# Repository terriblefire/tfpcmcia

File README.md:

# tfpcmcia

TerribleFire PCMCIA — a custom PCMCIA expansion card for the Amiga 1200 and Amiga 600, providing 4 MB fast RAM, an SD card interface, and 7 programmable RGB LEDs.

---

## Hardware

| Component | Part | Interface |
|-----------|------|-----------|
| Microcontroller | WCH CH32V307 (RISC-V, 144 MHz) | — |
| SPI RAM | APS6404L-3SQR, 4 MB | SPI1 @ 72 MHz |
| SD card | Standard microSD | SPI3 @ 36 MHz |
| LEDs | 7× APA102C RGB | GPIO (bit-banged) |

The card plugs into the Amiga's PCMCIA slot. The CH32V307 bridges the PCMCIA bus to an SPI RAM chip and SD card. The Amiga CPU accesses them entirely through memory-mapped reads and writes — the MCU handles all bus timing under interrupt.

---

## Memory Map

From the Amiga's perspective:

| Amiga address | Content | Notes |
|---------------|---------|-------|
| `$600000–$61FFFF` | Boot ROM (128 KB) | At power-on only; switches to SPIRAM after boot |
| `$620000–$9FFFFF` | SPIRAM (≈4 MB) | Fast RAM, available after driver init |
| `$A00000–$A001FF` | Attribute memory | PCMCIA CIS tuples (REG=1 accesses) |
| `$A20200–$A2023B` | I/O registers | Control, SPI, LED framebuffer |

The first 128 KB of SPIRAM overlaps the boot ROM window. After driver initialisation, `BOARD_CTRL` bit 0 is set, which switches that window from ROM to SPIRAM and makes the full 4 MB available as expansion memory.

---

## I/O Registers

All registers sit in PCMCIA I/O space. The Amiga's Gayle chip maps card I/O to `$A20000`; register byte offsets are relative to the card's I/O base (`0x220000`). The 68000 bus is 16 bits wide; each register occupies the upper byte of a 16-bit word (big-endian convention).

| Address | Offset | R/W | Name | Description |
|---------|--------|-----|------|-------------|
| `$A20200` | `0x200` | R/W | `SPI_DATA` | Write a byte to clock it out to the SD card; read to get the last byte clocked in |
| `$A20202` | `0x202` | W | `SPI_CS` | SD card chip select — `$00` = assert (active LOW), `$FF` = deassert |
| `$A20204` | `0x204` | R | `SPI_STATUS` | Bit 0: SD card detect (`1` = card present) |
| `$A20206` | `0x206` | R/W | `BOARD_CTRL` | Bit 0: `0` = boot ROM mapped, `1` = SPIRAM mapped; also controls LED mode |
| `$A20208` | `0x208` | R | `BOARD_ID` | Board identifier, always reads `$01` |
| `$A20220–$A2023B` | `0x220–0x23B` | W | `LED_FB` | LED framebuffer — 7 pixels × 4 bytes; see LED section |

---

## Boot Sequence

1. **CIS parsing** — Kickstart's `card.resource` reads the Card Information Structure from attribute memory (`$A00000`) and locates the `CISTPL_AMIGAXIP` (Execute-In-Place) tuple with the `AUTORUN` flag.

2. **XIP entry** — Kickstart calls `InitResident()` on the RomTag at `$600000`.

3. **Boot ROM init** — The ROM code:
   - Parses the embedded `tfpcmcia.device` (standard Amiga HUNK executable) from the ROM image
   - Allocates chip RAM, copies hunks, applies `HUNK_RELOC32` relocations
   - Calls `CacheClearU()` to flush CPU caches
   - Scans the loaded code for a RomTag and calls `InitResident()` on it

4. **Device init** — `tfpcmcia.device`:
   - Registers itself with Exec
   - Initialises the SD card via SPI (supports SDv1, SDv2, SDHC)
   - Creates an I/O task for asynchronous SD operations
   - Probes SPIRAM and, if present, adds a 1 MB block to the system free memory list (`AddMemList`, `MEMF_PUBLIC | MEMF_FAST`)
   - Scans the SD card for an RDB (Rigid Disk Block)

5. **RDB mounting** — Reads the partition table, loads filesystem handlers from LSEG blocks, creates DOS nodes via `MakeDosNode` / `AddBootNode`.

6. **DOS boot** — Calls `InitResident("dos.library")`. AmigaDOS picks the highest-priority bootable partition and continues the boot.

7. **ROM→SPIRAM switch** — After setup, the boot code copies a small trampoline onto the stack, flushes caches, jumps to the trampoline, then writes `BOARD_CTRL` bit 0 to switch the `$600000` window from ROM to SPIRAM. The full 4 MB is now available as fast RAM.

### A600 notes

On the A600 with Kickstart 3.0, the Gayle PCMCIA disable bit must be toggled in the DIAG handler to enable XIP boot. This is handled automatically by the boot ROM.

---

## SPIRAM

The 4 MB SPI RAM (APS6404L) is cached inside the CH32V307's 32 KB SRAM using a direct-mapped write-back cache:

- **512 cache lines × 64 bytes** = 32 KB cache
- **Address decomposition:** tag (7 bits) | line index (9 bits) | byte offset (6 bits)
- On a cache miss, any dirty line is evicted (written back via SPI burst) before the new line is fetched
- SPI transfers use 16-bit burst mode for maximum throughput (~9 MB/s)

From the Amiga driver's perspective, SPIRAM is transparent: ordinary memory reads and writes go through the cache without any special handling.

---

## LED System

Seven APA102C RGB LEDs are driven from two GPIO lines (clock + data) using a bit-banged serial protocol. The active LED mode is determined by `BOARD_CTRL` bit 0.

### KITT mode (bit 0 = 0, default)

Before the driver loads — and any time `BOARD_CTRL` bit 0 is clear — the firmware runs an autonomous scanner animation: a red spot bounces back and forth across all 7 LEDs with a short brightness tail, updating once per millisecond.

### Framebuffer mode (bit 0 = 1)

Once the driver sets `BOARD_CTRL` bit 0, the firmware switches to host-controlled mode. The Amiga driver paints arbitrary colours by writing to the `LED_FB` registers at `$A20220`.

#### LED framebuffer format

7 pixels, 4 bytes each (28 bytes total, `$A20220–$A2023B`). Each pixel occupies two consecutive 16-bit I/O writes:

| Write | Address offset | Upper byte [15:8] | Lower byte [7:0] |
|-------|---------------|-------------------|------------------|
| 1st | `0x220 + pixel×4` | Red | Green |
| 2nd | `0x222 + pixel×4` | Blue | Unused |

Pixel 0 is at `$A20220`, pixel 1 at `$A20224`, …, pixel 6 at `$A20238`.

---

## PCMCIA Interface (firmware)

The CH32V307 services every PCMCIA bus cycle under interrupt (`WCH-Interrupt-fast`). The interrupt handler runs entirely from RAM (`.ramtext` section) and is flattened / always-inlined to avoid register corruption in the fast-interrupt ABI.

Cycle types handled:

| Cycle | Action |
|-------|--------|
| Attribute memory read | Returns CIS tuple bytes (see below) |
| Common memory read, addr < 128 KB | Returns boot ROM byte pair |
| Common memory read, addr ≥ 128 KB | Returns SPIRAM data (cached) |
| Common memory write | Writes to SPIRAM (cached) |
| I/O read | Returns register value |
| I/O write | Updates register or LED framebuffer |

The Gayle chip swaps D0–D7 with D8–D15 relative to the 68000. Every value written to the data bus goes through `BUS16()` to compensate.

### CIS tuples (attribute memory)

| Tuple | Content |
|-------|---------|
| `CISTPL_DEVICE` (0x01) | SRAM, 250 ns, 4 MB |
| `CISTPL_VERS_1` (0x15) | Manufacturer: "TerribleFire", Product: "PCMCIA SD+RAM", Version: "1.0" |
| `CISTPL_FUNCID` (0x21) | Memory card |
| `CISTPL_AMIGAXIP` (0x91) | Execute-in-place, AUTORUN flag set |
| `CISTPL_END` (0xFF) | — |

---

## Amiga Driver (`tfpcmcia.device`)

Standard Amiga block device. Supports:

- `TD_READ64` / `TD_WRITE64` / `TD_SEEK64`
- `HD_SCSICMD`
- `NSCMD_DEVICEQUERY` / `NSCMD_TD_READ64` / `NSCMD_TD_WRITE64`

SD card geometry presented to the OS: 512-byte blocks, 16 heads, 32 sectors/track.

---

## Building

### Firmware

Open the project in MounRiver Studio (or use the provided Makefile under `firmware/`) and build for CH32V307. Flash with WCH-ISP (macOS binary included in `wchisp-macos-x64/`).

### Driver / boot ROM

```sh
cd driver
make
```

Produces `tfpcmcia.rom` — the 128 KB image that the firmware exposes as the boot ROM.

### MAME testing

The board is emulated as the `tfpcmcia` PCMCIA device:

```sh
mame a1200 -pcmcia tfpcmcia -hard2 sdcard.hdf -debug
```

To capture the driver's serial debug output:

```sh
mame a1200 -pcmcia tfpcmcia -hard2 sdcard.hdf \
  -rs232 null_modem -bitb socket.127.0.0.1:1234
# in another terminal:
nc -l 1234
```

Copy a freshly built ROM into MAME's ROM path:

```sh
cp driver/tfpcmcia.rom /path/to/mame/roms/tfpcmcia/
```

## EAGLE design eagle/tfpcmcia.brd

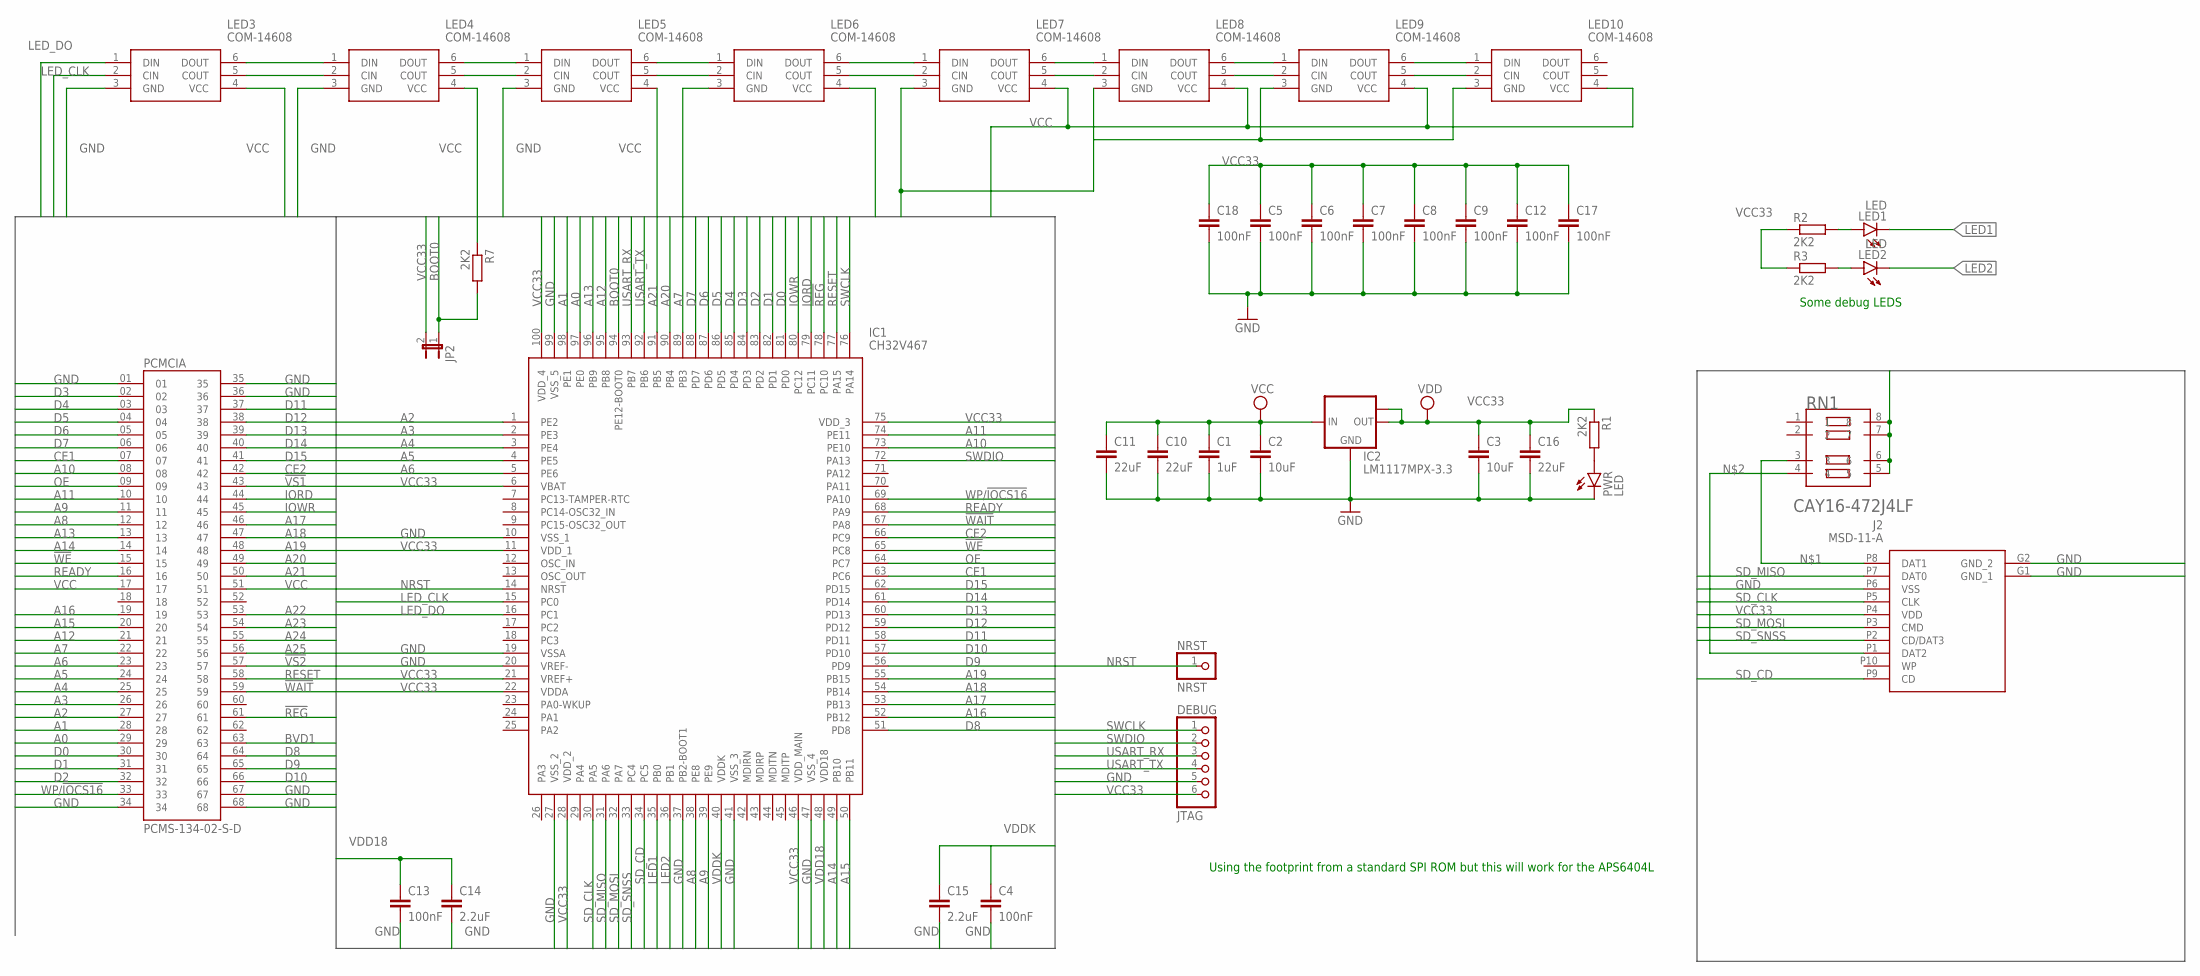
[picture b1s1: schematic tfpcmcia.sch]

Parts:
C1: 1uF; C1206
C2: 10uF; C0603
C3: 10uF; C1206
C4, C5, C6, C7, C8, C9, C12, C13, C17, C18: 100nF; C0603
C10, C11, C16: 22uF; C1206
C14, C15: 2.2uF; C0603
DEBUG: JTAG; 1X06_ROUND
IC1: CH32V467; QFP50P1600X1600X160-100N
IC2: LM1117MPX-3.3; SOT223
J2: MSD-11-A; MSD11A
JP2: JUMPER-2PTH; 1X02
LED1, LED2: LED; SML0805
LED3, LED4, LED5, LED6, LED7, LED8, LED9, LED10: COM-14608; SON75P200X200X100-6N
NRST: NRST; 1X01
PCMCIA: PCMS-134-02-S-D; SAMTEC_PCMS-134-02-S-D
PWR: LED; SML0805
R1, R2, R3, R7: 2K2; R0603
RN1: CAY16-472J4LF; RESCAXE80P320X160-8N

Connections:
!REG: IC1.78 (PC10), PCMCIA.61
!VS1: PCMCIA.43
!VS2: PCMCIA.57
!WAIT: IC1.67 (PA8), PCMCIA.59
!WE: IC1.65 (PC8), PCMCIA.15
A0: IC1.97 (PE0), PCMCIA.29
A1: IC1.98 (PE1), PCMCIA.28
A2: IC1.1 (PE2), PCMCIA.27
A3: IC1.2 (PE3), PCMCIA.26
A4: IC1.3 (PE4), PCMCIA.25
A5: IC1.4 (PE5), PCMCIA.24
A6: IC1.5 (PE6), PCMCIA.23
A7: IC1.89 (PB3), PCMCIA.22
A8: IC1.38 (PE8), PCMCIA.12
A9: IC1.39 (PE9), PCMCIA.11
A10: IC1.73 (PE10), PCMCIA.08
A11: IC1.74 (PE11), PCMCIA.10
A12: IC1.95 (PB8), PCMCIA.21
A13: IC1.96 (PB9), PCMCIA.13
A14: IC1.49 (PB10), PCMCIA.14
A15: IC1.50 (PB11), PCMCIA.20
A16: IC1.52 (PB12), PCMCIA.19
A17: IC1.53 (PB13), PCMCIA.46
A18: IC1.54 (PB14), PCMCIA.47
A19: IC1.55 (PB15), PCMCIA.48
A20: IC1.90 (PB4), PCMCIA.49
A21: IC1.91 (PB5), PCMCIA.50
A22: PCMCIA.53
A23: PCMCIA.54
A24: PCMCIA.55
A25: PCMCIA.56
BOOT0: IC1.94 (PE12-BOOT0), JP2.1, R7.2
BVD1: PCMCIA.63
CE1: IC1.63 (PC6), PCMCIA.07
CE2: IC1.66 (PC9), PCMCIA.42
D0: IC1.81 (PD0), PCMCIA.30
D1: IC1.82 (PD1), PCMCIA.31
D2: IC1.83 (PD2), PCMCIA.32
D3: IC1.84 (PD3), PCMCIA.02
D4: IC1.85 (PD4), PCMCIA.03
D5: IC1.86 (PD5), PCMCIA.04
D6: IC1.87 (PD6), PCMCIA.05
D7: IC1.88 (PD7), PCMCIA.06
D8: IC1.51 (PD8), PCMCIA.64
D9: IC1.56 (PD9), PCMCIA.65
D10: IC1.57 (PD10), PCMCIA.66
D11: IC1.58 (PD11), PCMCIA.37
D12: IC1.59 (PD12), PCMCIA.38
D13: IC1.60 (PD13), PCMCIA.39
D14: IC1.61 (PD14), PCMCIA.40
D15: IC1.62 (PD15), PCMCIA.41
GND: C1.2, C2.2, C3.2, C4.2, C5.2, C6.2, C7.2, C8.2, C9.2, C10.2, C11.2, C12.2, C13.2, C14.2, C15.2, C16.2, C17.2, C18.2, DEBUG.5, IC1.10 (VSS_1), IC1.19 (VSSA), IC1.20 (VREF-), IC1.27 (VSS_2), IC1.37 (PB2-BOOT1), IC1.41 (VSS_3), IC1.47 (VSS_4), IC1.99 (VSS_5), IC2.1 (GND), J2.G1 (GND_1), J2.G2 (GND_2), J2.P6 (VSS), LED3.3 (GND), LED4.3 (GND), LED5.3 (GND), LED6.3 (GND), LED7.3 (GND), LED8.3 (GND), LED9.3 (GND), LED10.3 (GND), PCMCIA.01, PCMCIA.34, PCMCIA.35, PCMCIA.36, PCMCIA.67, PCMCIA.68, PWR.C, R7.1
IORD: IC1.79 (PC11), PCMCIA.44
IOWR: IC1.80 (PC12), PCMCIA.45
LED1: IC1.35 (PB0), LED1.C
LED2: IC1.36 (PB1), LED2.C
LED_CLK: IC1.15 (PC0), LED3.2 (CIN)
LED_DO: IC1.16 (PC1), LED3.1 (DIN)
unnamed: J2.P8 (DAT1), RN1.3
unnamed: J2.P1 (DAT2), RN1.4
unnamed: LED9.5 (COUT), LED10.2 (CIN)
unnamed: LED9.6 (DOUT), LED10.1 (DIN)
unnamed: LED1.A, R2.2
unnamed: LED2.A, R3.2
unnamed: LED4.5 (COUT), LED5.2 (CIN)
unnamed: LED4.6 (DOUT), LED5.1 (DIN)
unnamed: LED5.6 (DOUT), LED6.1 (DIN)
unnamed: LED5.5 (COUT), LED6.2 (CIN)
unnamed: LED3.5 (COUT), LED4.2 (CIN)
unnamed: LED3.6 (DOUT), LED4.1 (DIN)
unnamed: LED6.5 (COUT), LED7.2 (CIN)
unnamed: PWR.A, R1.2
unnamed: LED6.6 (DOUT), LED7.1 (DIN)
unnamed: LED7.6 (DOUT), LED8.1 (DIN)
unnamed: LED7.5 (COUT), LED8.2 (CIN)
unnamed: LED8.5 (COUT), LED9.2 (CIN)
unnamed: LED8.6 (DOUT), LED9.1 (DIN)
NRST: IC1.14 (NRST), NRST.1
OE: IC1.64 (PC7), PCMCIA.09
READY: IC1.68 (PA9), PCMCIA.16
RESET: IC1.77 (PA15), PCMCIA.58
SD_CD: IC1.34 (PC5), J2.P9 (CD)
SD_CLK: IC1.30 (PA5), J2.P5 (CLK)
SD_MISO: IC1.31 (PA6), J2.P7 (DAT0)
SD_MOSI: IC1.32 (PA7), J2.P3 (CMD)
SD_SNSS: IC1.33 (PC4), J2.P2 (CD/DAT3)
SWCLK: DEBUG.1, IC1.76 (PA14)
SWDIO: DEBUG.2, IC1.72 (PA13)
USART_RX: DEBUG.3, IC1.93 (PB7)
USART_TX: DEBUG.4, IC1.92 (PB6)
VCC: C1.1, C2.1, C10.1, C11.1, IC2.3 (IN), LED3.4 (VCC), LED4.4 (VCC), LED5.4 (VCC), LED6.4 (VCC), LED7.4 (VCC), LED8.4 (VCC), LED9.4 (VCC), LED10.4 (VCC), PCMCIA.17, PCMCIA.51
VCC33: C3.1, C5.1, C6.1, C7.1, C8.1, C9.1, C12.1, C16.1, C17.1, C18.1, DEBUG.6, IC1.6 (VBAT), IC1.11 (VDD_1), IC1.21 (VREF+), IC1.22 (VDDA), IC1.28 (VDD_2), IC1.46 (VDD_MAIN), IC1.75 (VDD_3), IC1.100 (VDD_4), IC2.2 (OUT), IC2.TAB (OUT1), J2.P4 (VDD), JP2.2, R1.1, R2.1, R3.1, RN1.5, RN1.6, RN1.7, RN1.8
VDD18: C13.1, C14.1, IC1.48 (VDD18)
VDDK: C4.1, C15.1, IC1.40 (VDDK)
WP/!IOCS16: IC1.69 (PA10), PCMCIA.33

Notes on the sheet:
Using the footprint from a standard SPI ROM but this will work for the APS6404L
Some debug LEDS

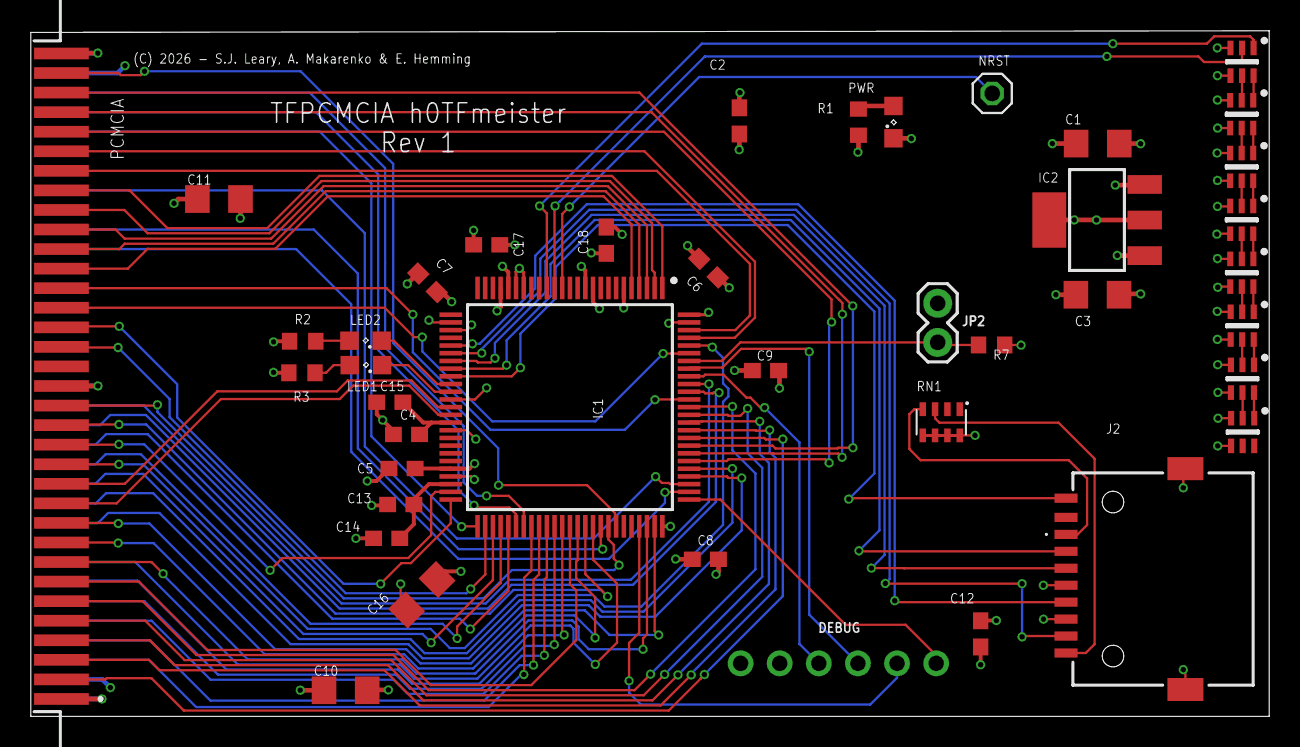
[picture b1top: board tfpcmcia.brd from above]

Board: 4 copper layers, 80.4 x 44.5 mm, 41 parts (0 on the bottom side), 88 nets.

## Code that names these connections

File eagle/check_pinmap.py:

#!/usr/bin/env python3
"""Check IC1 wiring in tfpcmcia.sch against the CH32V467VET6 target pin map.

Target map is docs/ch32v467-migration-plan.md section 7.
Reads the schematic directly, so no netlist regeneration is needed.

    .venv/bin/python check_pinmap.py [tfpcmcia.sch]

Exit status is 0 only when every pin matches.
"""
import sys
from pathlib import Path
from lxml import etree

HERE = Path(__file__).resolve().parent
SCH = Path(sys.argv[1]) if len(sys.argv) > 1 else HERE / "tfpcmcia.sch"
LBR = HERE / "SamacSys_Parts.lbr"
PART = "IC1"

# --- target: pin name -> net name ----------------------------------------
TARGET = {}
for i in range(16):
    TARGET[f"PD{i}"] = f"D{i}"
for i in range(7):
    TARGET[f"PE{i}"] = f"A{i}"                       # PE0-PE6  -> A0-A6
TARGET["PB3"] = "A7"                                 # fills the PE7 gap
for i in range(4):
    TARGET[f"PE{8+i}"] = f"A{8+i}"                   # PE8-PE11 -> A8-A11
for i in range(8):
    TARGET[f"PB{8+i}"] = f"A{12+i}"                  # PB8-PB15 -> A12-A19
TARGET["PB4"], TARGET["PB5"] = "A20", "A21"
TARGET.update({                                      # control in
    "PC6": "CE1", "PC7": "OE", "PC8": "!WE", "PC9": "CE2",
    "PC10": "!REG", "PC11": "IORD", "PC12": "IOWR", "PA15": "RESET",
})
TARGET.update({                                      # control out
    "PA8": "!WAIT", "PA9": "READY", "PA10": "WP/!IOCS16",
})
TARGET.update({                                      # peripherals
    "PA5": "SD_CLK", "PA6": "SD_MISO", "PA7": "SD_MOSI",
    "PC4": "SD_SNSS", "PC5": "SD_CD",
    "PC0": "LED_CLK", "PC1": "LED_DO",
    "PB0": "LED1", "PB1": "LED2",
    "PB6": "USART_TX", "PB7": "USART_RX",
    "PA13": "SWDIO", "PA14": "SWCLK",
    "PE12-BOOT0": "BOOT0", "NRST": "NRST",
})
for p in ("VSS_1", "VSS_2", "VSS_3", "VSS_4", "VSS_5", "VSSA", "VREF-"):
    TARGET[p] = "GND"
# BOOT1 must be strapped low: with BOOT0 high (JP2 fitted for ISP) a floating
# BOOT1 leaves the boot source indeterminate. Datasheet Note 5 also asks for a
# pull-down to avoid extra current in low-power modes.
TARGET["PB2-BOOT1"] = "GND"
for p in ("VDD_1", "VDD_2", "VDD_3", "VDD_4", "VDD_MAIN", "VDDA", "VREF+", "VBAT"):
    TARGET[p] = "VCC33"
TARGET["VDDK"] = "VDDK"      # own rail, 0.1uF || 2.2uF to GND
TARGET["VDD18"] = "VDD18"    # own rail, 0.1uF || 2.2uF to GND

# pins that must be left unconnected
NC = {
    "MDIRN": "Ethernet unused", "MDIRP": "Ethernet unused",
    "MDITN": "Ethernet unused", "MDITP": "Ethernet unused",

    "PA0-WKUP": "spare", "PA1": "spare", "PA2": "spare", "PA3": "spare",
    # audio output stage (IC4/C13/C14) removed - BVD2 no longer driven
    "PA4": "spare (audio stage removed)",
    # USB breakout jumper JP1 removed - programming is SWD + UART only
    "PA11": "spare (USB removed)", "PA12": "spare (USB removed)",
    "PC2": "spare", "PC3": "spare",
    "PC13-TAMPER-RTC": "unused", "PC14-OSC32_IN": "unused",
    "PC15-OSC32_OUT": "unused",
    "OSC_IN": "unused (internal RC)", "OSC_OUT": "unused (internal RC)",
}

# non-5V-tolerant pins: nothing on the Amiga bus may land here
NON_FT = ({f"PA{i}" for i in range(8)} | {"PA0-WKUP", "PA11", "PA12"}
          | {"PB0", "PB1", "PB6", "PB7"} | {f"PC{i}" for i in range(6)}
          | {"PC13-TAMPER-RTC", "PC14-OSC32_IN", "PC15-OSC32_OUT"})
AMIGA = ({f"A{i}" for i in range(22)} | {f"D{i}" for i in range(16)}
         | {"CE1", "CE2", "OE", "!WE", "!REG", "IORD", "IOWR", "RESET",
            "!WAIT", "READY", "WP/!IOCS16"})


def main():
    root = etree.parse(str(SCH)).getroot()
    lbr = etree.parse(str(LBR)).getroot()
    pad = {c.get("pin"): int(c.get("pad")) for c in
           lbr.find(".//deviceset[@name='CH32V467VET6']").findall(".//connect")}

    actual = {}
    for net in root.findall(".//net"):
        for seg in net.findall("segment"):
            for pr in seg.findall("pinref"):
                if pr.get("part") == PART:
                    actual.setdefault(pr.get("pin"), []).append(net.get("name"))

    wrong, missing, extra, dupe = [], [], [], []
    for pin, want in sorted(TARGET.items(), key=lambda kv: pad.get(kv[0], 0)):
        got = actual.get(pin)
        if got is None:
            missing.append((pad.get(pin), pin, want))
        elif len(got) > 1:
            dupe.append((pad.get(pin), pin, got))
        elif got[0] != want:
            wrong.append((pad.get(pin), pin, got[0], want))
    for pin, why in sorted(NC.items(), key=lambda kv: pad.get(kv[0], 0)):
        if pin in actual:
            extra.append((pad.get(pin), pin, actual[pin][0], why))

    unsafe = [(pad.get(p), p, n[0]) for p, n in actual.items()
              if p in NON_FT and n[0] in AMIGA]

    ok = len(TARGET) - len(wrong) - len(missing) - len(dupe)
    print(f"IC1 / CH32V467VET6 pin map: {ok}/{len(TARGET)} correct\n")

    def show(title, rows, fmt):
        if rows:
            print(f"{title} ({len(rows)})")
            for r in rows:
                print("   " + fmt(r))
            print()

    show("UNSAFE - Amiga bus signal on a non-5V-tolerant pin", unsafe,
         lambda r: f"pad {r[0]:>3}  {r[1]:<16} {r[2]}")
    show("WRONG NET", wrong,
         lambda r: f"pad {r[0]:>3}  {r[1]:<16} {r[2]:<14} -> should be {r[3]}")
    show("NOT CONNECTED", missing,
         lambda r: f"pad {r[0]:>3}  {r[1]:<16} needs {r[2]}")
    show("SHOULD BE UNCONNECTED", extra,
         lambda r: f"pad {r[0]:>3}  {r[1]:<16} on {r[2]:<14} ({r[3]})")
    show("PIN ON MULTIPLE NETS", dupe,
         lambda r: f"pad {r[0]:>3}  {r[1]:<16} {r[2]}")

    bad = bool(wrong or missing or extra or dupe or unsafe)
    print("FAIL" if bad else "PASS - pin map matches the target")
    return 1 if bad else 0


if __name__ == "__main__":
    sys.exit(main())

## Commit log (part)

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2026-01-29 Adding the cam file
2026-01-29 Finished routing, unchecked schematic
2026-01-29 updated the audio section
2026-01-29 fixed BOOT0
2026-01-29 Updated READY signal and updated pinout specs
2026-01-30 added blinkenlights and gathered notes on spi ram usage
2026-01-30 tightened DRC
2026-03-08 Add tfpcmcia.device driver and boot ROM sources
2026-03-08 Add serial debug output instructions to README
2026-03-12 refactor PCMCIA handler: address decode + typed dispatch functions
    - Decode full 22-bit address (GPIOE A0-A15, GPIOB[0:5] A16-A21)
    - Dispatch to PCMCIA_Memory_Read/Write and PCMCIA_Reg_Read/Write
    - Write stubs NOP; reads return BEEF (common) and address echo (attribute)
    - Mark all dispatch functions always_inline — required because WCH-Interrupt-fast
    does not save caller-saved registers, so any real call produces garbage
2026-03-12 add initial firmware: CH32V307 PCMCIA bus emulation returning BEEF/BABE
    - Dockerised build using local MRS toolchain (riscv-none-embed-gcc)
    - EXTI9_5 VTF interrupt handler drives data bus on UDS/LDS assertion
    - Common memory returns 0xBEEF, attribute memory returns 0xBABE
    - BUS16() macro compensates for Gayle byte-lane swap on A600/A1200
    - UART debug on PA9 at 115200, heartbeat LED on PC8
    - Top-level Makefile delegates build/clean to Docker container
2026-03-12 untrack eagle generated outputs, update gitignore
    BOM CSVs, CPL, netlist, Eagle scripts, gerber zip and folder are all
    produced by the eagle/Makefile and should not be in version control.
2026-03-13 Board updates for revision 1
2026-03-15 Driver read code wokring and attributes implemented
2026-03-19 Fix SD card SPI init and PCMCIA handler for real hardware
    Driver:
    - Move SPI registers to IO space (0xA20200)
    - Fix SdReadSector/SdWriteSector addressing: use block address
    directly for SDHC (was incorrectly shifting lba << 9)
    - Add 8 dummy clocks after every CS deassert to allow SD card
    to release MISO before next command
2026-03-19 Pass card type to SdReadSector/SdWriteSector as parameter
    Removes static sd_type from spi.c and passes cardType explicitly,
    allowing correct address calculation (block vs byte) based on card type
    at each call site via db->db_CardType.
2026-03-19 Toggle CS between ACMD41 retries, increase SDv2 retry count
    SD spec requires CS to be deasserted between commands in SPI mode.
    Add CS toggle before each CMD55/ACMD41 pair in both SDv2 and SDv1
    init loops. Increase SDv2 retry count to 100000 to cover the card's
    1-second initialisation window.
2026-03-19 Drive LED2 from SD card chip select
    LED2 mirrors the SD CS line: on when CS is asserted (low), off when
    CS is deasserted (high).
2026-03-19 Adapt SD driver from FPGAArcade card.c
    Rewrite spi.c based on the FPGAArcade Replay card.c (MPL 2.0):
    - 3-attempt init with 100ms delay between retries
    - 1-second ACMD41 timeout loop (~10000 iterations)
    - MMC support via CMD1
    - CMD16 block length set for non-SDHC cards
    - CMD13 post-read/write status check
2026-03-19 Reduce IOR data setup delay to 10 NOPs (~70ns)
2026-03-20 top dog simon
2026-03-20 Update README for 128KB ROM and I/O space registers
2026-03-21 Add SPIRAM AddMemList, pipelined SPI read/write, and PCMCIA refactor
    - Probe APS6404L at 0x620000 and add 3.875MB to AmigaOS as MEMF_PUBLIC|MEMF_FAST at priority -20
    - Rewrite SPIRAM_Read16/Write16 with pipelined SPI (RXNE/TXE interleaved) and add SPIRAM_Write8
    - Place PCMCIA_Handler and PCMCIA_PollLoop in .ramtext for faster execution
    - Expand ROM window to 128KB (0x20000), fix word-align mask
    - Refactor PCMCIA_Handler: early exit on idle strobe, fast OE path for attr/reg reads, add WE write path for SPIRAM
    - Rename Init_PCMCIA -> PCMCIA_Init, extract poll loop to PCMCIA_PollLoop
2026-03-21 increased spiram speed to 36Mhz and switched to 16 bit words for word accesses
2026-03-21 Add direct-mapped SPIRAM read cache (8 × 1 KB lines)
    SPIRAM_Read16 now checks an 8-line direct-mapped cache in CH32 SRAM
    before issuing any SPI transaction. On a miss, SPIRAM_ReadBurst fills
    the full 1 KB line in a single pipelined 16-bit SPI burst (~228 µs).
    Writes remain write-through; SPIRAM_CacheInvalidate is called after
    every Write16 and Write8 to keep the cache coherent.
2026-03-22 Add PcmciaConstants struct for RISC-V GP-relative optimisation
    Replace large immediate constants in PCMCIA_Handler and helpers with
    fields from a PcmciaConstants struct (K) placed in .sdata, allowing the
    compiler to reach each value with a single GP-relative lw instead of
    a lui+addi pair. Switch to poll-loop mode (VTF IRQ disabled), -Ofast,
    and ilp32 ABI.
2026-03-22 Add write-back SPIRAM cache and limit OS memory to 1MB
    - spiram.h: replace single-word SPI functions with a 512-line x 64-byte
    direct-mapped write-back cache (32KB total in SRAM). Writes go to the
    cache only; SPIRAM is written on dirty-line eviction. SPIRAM_ReadBurst
    and SPIRAM_WriteBurst handle 64-byte cache line fills and flushes in
    pipelined 16-bit SPI mode. WriteBurst drains all N+2 RX words to avoid
    leaving stale data in the SPI FIFO between transactions.
2026-03-23 Add dual DIAG+XIP CIS boot flow with BOARD_CTRL switching
2026-03-23 Boost tfpcmcia boot priority by +64 to always boot before internal drives
2026-03-23 Fix XIP boot on KS 3.0 by toggling Gayle PCMCIA disable bit in DIAG handler
2026-03-23 run topdog with SR=000
2026-03-26 working on the a600
2026-03-26 reverted XIP on A600
2026-03-26 Add LED mode switching and document full functionality
    - firmware: add APA102 framebuffer mode (7 RGB pixels via IO writes at
    $A20220); KITT animation is default, switches to host-controlled FB
    when BOARD_CTRL bit 0 is set by the driver
    - firmware: expose PCMCIA_BoardCtrl() getter and led_fb[] array
    - README: complete rewrite covering hardware, memory map, all I/O
    registers, boot sequence, SPIRAM cache, LED modes, PCMCIA interface,
2026-03-27 Add green ramp LED mode, PB13 reset interrupt, and fix BOARD_CTRL writes
    - LED: add APA102_GreenRamp (4s linear ramp to full green, holds)
    - LED: expand dispatch to 4-mode switch on full BOARD_CTRL value (0=ramp, 1=KITT, 2=nop, 3=FB)
    - LED: reset frame counter on mode change; frame increments every tick
    - Firmware: wire EXTI13 (PB13/RESET falling edge) to PCMCIA_ResetHandler at NVIC priority 0x40
    - Firmware: PCMCIA_ResetHandler clears board_ctrl and deasserts SD CS on card reset
    - Driver: fix BOARD_CTRL register address (A00206 -> A20206); write 0 on init, remove spurious write in trampoline
2026-03-27 Remove non-tfpcmcia BootNodes from MountList before starting DOS
2026-03-28 more A600 fixes. its very sulky. probably wont work in the morning
2026-03-28 another minor a600 fix
2026-03-28 fixed iow on A600. added amber blinkenlights effect
2026-04-03 makefile update
2026-04-04 Fix the cache writeback issue
2026-04-04 Makefile fixes
2026-04-04 kill caches, add CIA syncs

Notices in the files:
eagle/tfpcmcia.brd:
(C) 2026 - S.J. Leary, A. Makarenko & E. Hemming
parts and their libraries:
microbuilder: This work is placed in the public domain, and may be freely used for commercial and non-commercial work with the following conditions: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
SparkFun-Retired: Licensing: Creative Commons ShareAlike 4.0 International - https://creativecommons.org/licenses/by-sa/4.0
